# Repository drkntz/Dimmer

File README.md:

# Dimmer
A peripheral for microprocessor control of 120V AC.

This project originally started in 2020 as a proof of concept for an AC motor controller, but can be used for many projects involving variable duty cycle AC control. It supports operation for low current (<5A) AC driving as a low-side switch. 

The original board included both an AC triac control and a 5V non-isolated power supply (linkswitch LNK3206). This unit was meant for use in situations where the device is fully enclosed in an insulated housing. However, if fully isolated operation is desired, the Dimmer may be used with an external 5V power supply, as it contains optically isolated triac drive and zero-crossing detection circuits.

The software in this project was used for a raspberry pi to connect with the rev1 board. 

TODO: Schematic printout needs some work, is missing interface header J1. Rev2 will fix this.

# Schematic rev 1

# PCB Layout rev 1

# PCB 3-D Model rev 1

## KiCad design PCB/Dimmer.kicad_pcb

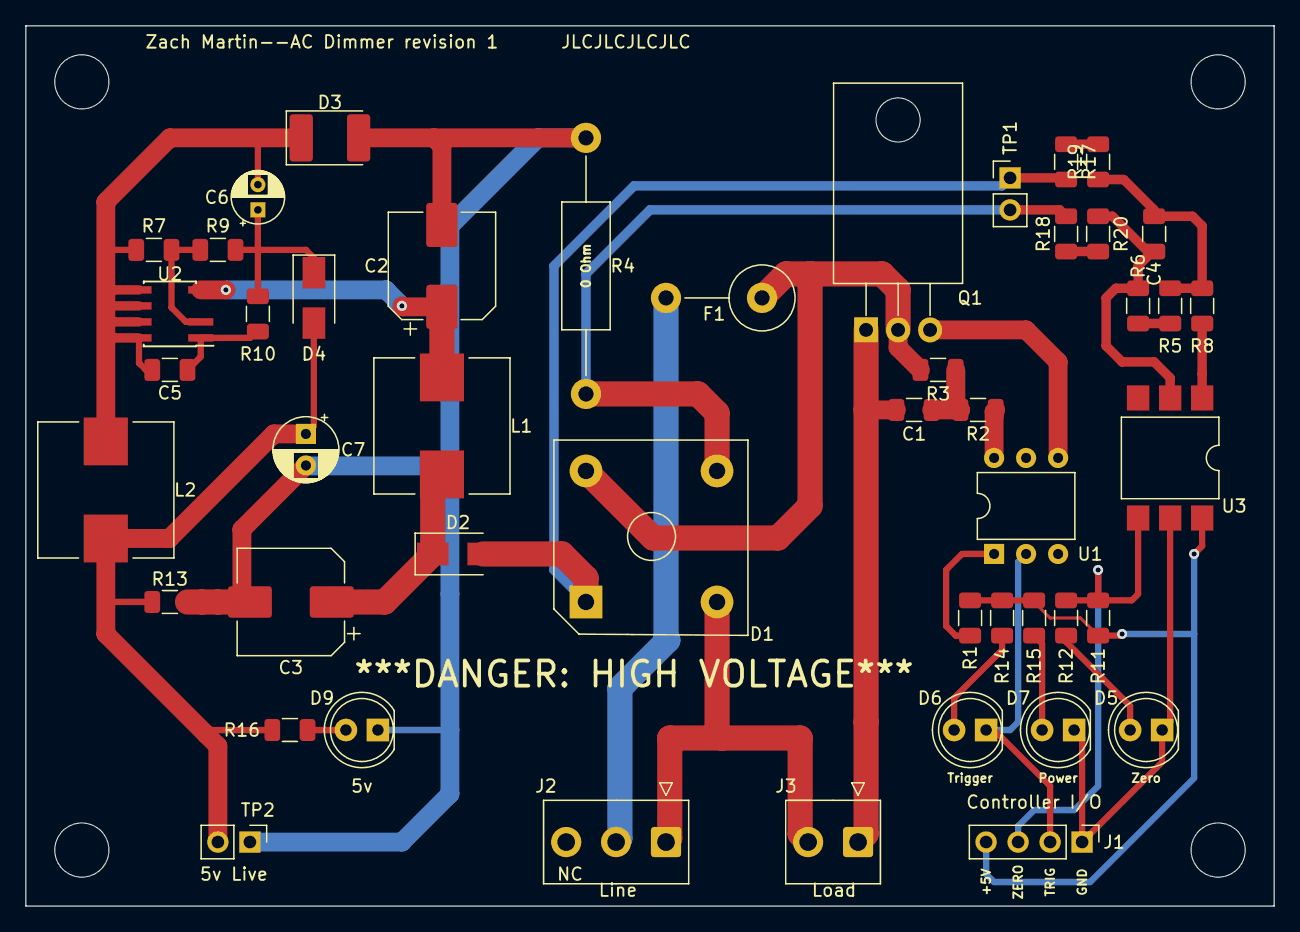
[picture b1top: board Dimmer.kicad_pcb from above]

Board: 2 copper layers, 99.1 x 69.8 mm, 47 parts (0 on the bottom side), 32 nets.

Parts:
C1: 200nF; C_1206_3216Metric
C2, C3: 4.7uF; CP_Elec_8x10
C4: 10nF; C_1206_3216Metric
C5: 100nF; C_1206_3216Metric
C6: 10uF; CP_Radial_D4.0mm_P2.00mm
C7: 100uF; CP_Radial_D5.0mm_P2.50mm
D1: D_Bridge_+A-A; Diode_Bridge_Vishay_KBPC6
D2, D4: US1M; D_SMA
D3: SK510; D_2114_3652Metric_Pad1.85x3.75mm_HandSolder
D5: zcross; LED_D5.0mm
D6: Trigger; LED_D5.0mm
D7: EXT_PWR; LED_D5.0mm
D9: 5v_live; LED_D5.0mm
F1: 2A; R_Axial_DIN0516_L15.5mm_D5.0mm_P7.62mm_Vertical
J1: Conn_01x04; PinHeader_1x04_P2.54mm_Vertical
J2: Conn_01x03; TE_826576-3_1x03_P3.96mm_Vertical
J3: Load (motor); TE_826576-2_1x02_P3.96mm_Vertical
L1: 560uH; L_Wuerth_HCI-1030
L2: 680uH; L_Wuerth_HCI-1030
Q1: SC146D; TO-220-3_Horizontal_TabDown
R1, R11, R13: 1k; R_1206_3216Metric
R2: 100R; R_1206_3216Metric
R3: 1.2k; R_1206_3216Metric
R4: 8R; R_Axial_DIN0411_L9.9mm_D3.6mm_P20.32mm_Horizontal
R5, R6, R8, R17, R18, R19, R20: 10k; R_1206_3216Metric
R7: 2.49k; R_1206_3216Metric
R9: 4.22k; R_1206_3216Metric
R10: 15k; R_1206_3216Metric
R12, R14, R15, R16: 500R; R_1206_3216Metric
TP1: Zcross_TP; PinHeader_1x02_P2.54mm_Vertical
TP2: 5v_live_TP; PinHeader_1x02_P2.54mm_Vertical
U1: MOC3023M; DIP-6_W7.62mm
U2: LNK3206D; PowerIntegrations_SO-8C
U3: H11L1; SMDIP-6_W9.53mm

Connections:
+5V: J1.4, R1.1, R11.2, R14.2, R15.2, U3.6
GND: D5.1, D7.1, J1.1, U3.5
GND2: C2.2, C3.2, C7.2, D3.2, D9.1, R4.1, R13.2, TP2.1
unnamed: C1.1, R2.1, R3.2
unnamed: C1.2, J3.1, Q1.1
unnamed: C2.1, L1.1, U2.4
unnamed: C3.1, D2.1, L1.2
unnamed: C4.1, R5.1, R8.1, R19.1
unnamed: C4.2, R6.2, R20.1, U3.2
unnamed: C5.1, R10.2, U2.1
unnamed: C5.2, C6.2, D3.1, L2.1, R7.1, U2.5, U2.6, U2.7, U2.8
unnamed: C6.1, D4.1, R9.1, R10.1
unnamed: C7.1, D4.2, L2.2, R13.1, R16.1, TP2.2
unnamed: D1.1, D2.2, R17.2, TP1.1
unnamed: D1.2, J2.1, J3.2
unnamed: D1.3, R4.2, R18.2, TP1.2
unnamed: D1.4, F1.1, Q1.2, R3.1
unnamed: D5.2, R12.2
unnamed: D6.2, R14.1
unnamed: D7.2, R15.1
unnamed: D9.2, R16.2
unnamed: F1.2, J2.2
unnamed: Q1.3, U1.4
unnamed: R1.2, U1.1
unnamed: R2.2, U1.6
unnamed: R5.2, R6.1
unnamed: R7.2, R9.2, U2.2
unnamed: R8.2, U3.1
unnamed: R17.1, R19.2
unnamed: R18.1, R20.2
trigger: D6.1, J1.2, U1.2
zcross: J1.3, R11.1, R12.1, U3.4

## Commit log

2020-08-18 Initial commit 18 Aug 2020 ZM
2020-08-18 Updating software version to version containing interrupt handlers instead of polling and messy multithreading.
2020-08-18 Removed backup software, changed schematic to improve circuit. No change on PCB.
2020-08-19 Updated schematic, software to clarify speed buttons
2020-08-21 Cleanup
2020-09-30 Latest version before switching PCs
2022-01-20 Migrating from personal gitserver
2022-01-20 re-organize file structure
2022-01-20 removed uneeded file
2022-11-18 general clean-up
2022-11-18 added init date to readme
